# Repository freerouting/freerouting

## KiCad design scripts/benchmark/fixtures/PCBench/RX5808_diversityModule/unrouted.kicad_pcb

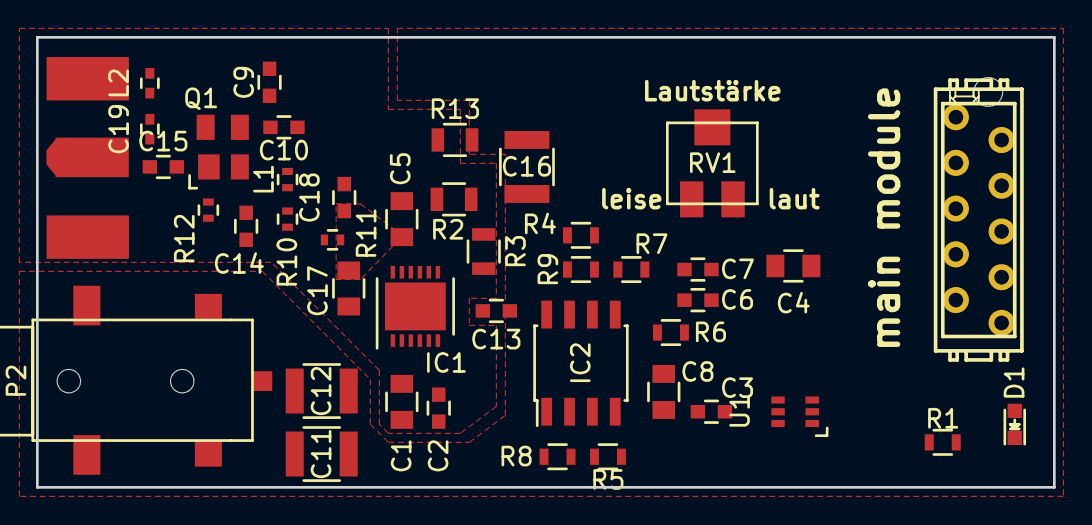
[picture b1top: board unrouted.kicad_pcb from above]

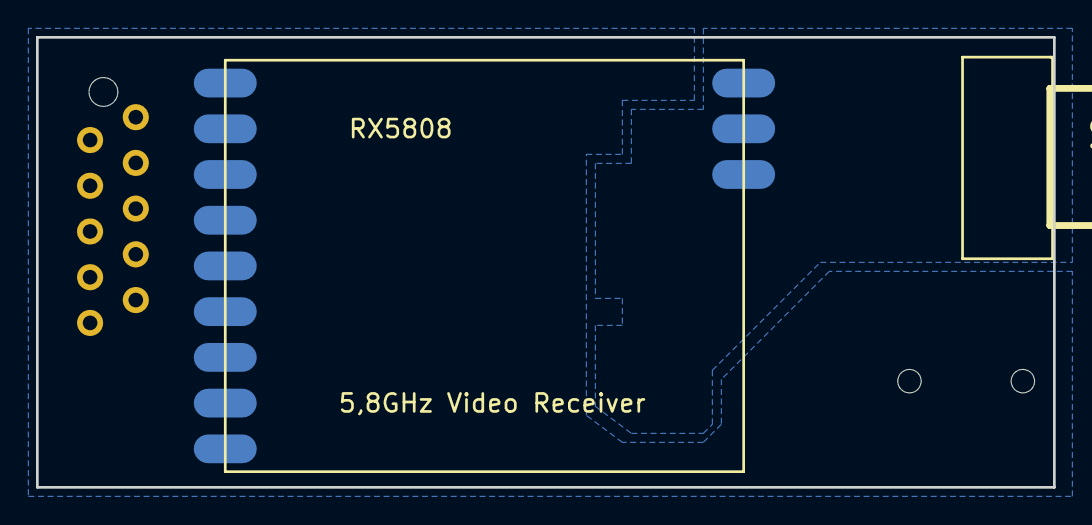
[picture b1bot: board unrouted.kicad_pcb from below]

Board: 2 copper layers, 56.5 x 25.0 mm, 44 parts (2 on the bottom side), 33 nets, no tracks yet.

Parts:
C1, C4, C5, C17: 10u; C_0805
C2: 10n; C_0603
C3, C13, C18: 100n; C_0603
C6, C7: 1u; C_0603
C8: 22u; C_0805
C9, C10: 1p; C_0603
C11, C12, C16: 100µ; C_1210
C14: 33pF; C_0603
C15: 22p; C_0603
C19: 2,2pF; C_0402
D1: red; LED_0603
IC1: LP38798; DFN-12-1EP_4x4mm_Pitch0.5mm
IC2: TDA1308A; SOIC-8_3.9x4.9mm_Pitch1.27mm
L1: 1,8nH; R_0402
L2: 1,8nH; C_0402
P1: CONN_02X05; MICROMATCH-10
P2: CONN_01X03; LUM1503-03
Q1: BFP840; SOT-143
R1: 220; R_0603
R2: 21k 0,1%; R_0805
R3: 14k 0,1%; R_0805
R4, R5: 10k; R_0603
R6, R7: 3,9k; R_0603
R8, R9: 39k; R_0603
R10, R11: 51; R_0402
R12: 27k; R_0402
R13: 0; R_0805
RV1: POT; Poti-SMD-Model-23A
SMA_E1: SMA_EDGE; SMA_EDGE_Johnson_142-0701-801
U1: sn74lvc1g3157; SC-70-6
U2: RX5808

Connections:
+5V: C1.1, C3.1, C4.1, C13.1, C16.1, IC1.1, IC1.2, IC1.3, IC1.5, IC2.8, P1.1, R4.1, U1.5, U2.8
/+3,0V: C5.1, C17.1, C18.1, IC1.10, IC1.11, IC1.12, R11.2
/audio1: P1.6, U1.3
/clk: P1.7, U2.6
/data: P1.3, U2.4
/rssi: P1.8, U2.9
/ss: P1.5, U2.5
/switch: D1.2, P1.9, U1.6
/video2: P1.4, U2.11
GND: C3.2, C4.2, C8.2, C13.2, C16.2, IC2.4, P1.2, P2.1, R1.2, R5.2, R13.1, RV1.3, U1.2, U2.7, U2.12
GNDA: C1.2, C2.2, C5.2, C9.2, C14.1, C17.2, C18.2, IC1.6, IC1.7, IC1.13, L2.2, Q1.2, Q1.4, R3.2, R13.2, SMA_E1.0, SMA_E1.2, U2.1, U2.3
unnamed: C2.1, IC1.4
unnamed: C6.1, R6.2
unnamed: C6.2, C7.2, RV1.2
unnamed: C7.1, R7.2
unnamed: C8.1, IC2.2, IC2.3, IC2.5, R4.2, R5.1, R6.1, R8.2
unnamed: C9.1, C10.1, L1.2, Q1.3
unnamed: C10.2, U2.2
unnamed: C11.1, IC2.1, R8.1
unnamed: C11.2, P2.2
unnamed: C12.1, IC2.7, R9.1
unnamed: C12.2, P2.3
unnamed: C14.2, R10.1, R11.1, R12.2
unnamed: C15.1, C19.1, SMA_E1.1
unnamed: C15.2, Q1.1, R12.1
unnamed: C19.2, L2.1
unnamed: D1.1, R1.1
unnamed: IC1.8, R2.2, R3.1
unnamed: IC1.9, R2.1
unnamed: IC2.6, R7.1, R9.2
unnamed: L1.1, R10.2
unnamed: RV1.1, U1.4
unnamed: U1.1, U2.10

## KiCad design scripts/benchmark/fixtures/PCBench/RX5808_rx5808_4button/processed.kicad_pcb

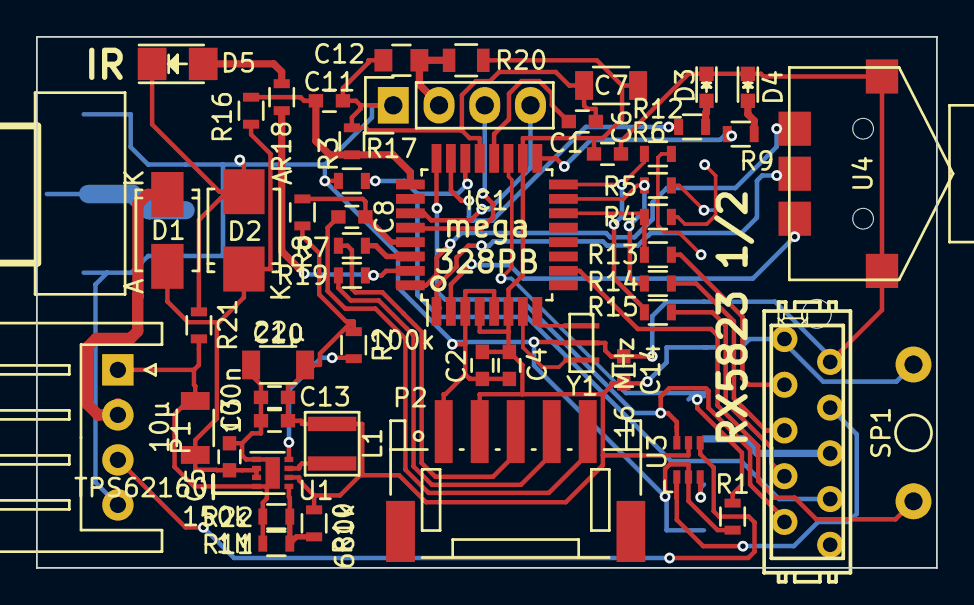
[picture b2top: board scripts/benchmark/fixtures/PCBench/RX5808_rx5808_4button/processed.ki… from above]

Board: 2 copper layers, 50.0 x 29.5 mm, 54 parts (1 on the bottom side), 47 nets.

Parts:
C1, C2, C3, C4, C6, C8, C9, C11, C13, C14: 100n; C_0603
C5: 10µ; C_1206
C7, C10: 22µ; C_1206
C12: 4,7u; C_0805
D1: B 140 F; SMA_Standard
D2: P6SMB 18A SMD; SMB_Standard
D3, D4: grün; LED_0603
D5: IR_EMITTER; LED_1206
IC1: ATMEGA328-A; TQFP-32_7x7mm_Pitch0.8mm
L1: 2,2µH 1,5A; NR3015
P1: CONN_01X04; JST_XH_S04B-XH-A_04x2.50mm_Angled
P2: CONN_01X05; JST_PH_S5B-PH-SM4-TB_05x2.00mm_Angled
P6: CONN_01X04; Pin_Header_Straight_1x04
P7: CONN_02X05; MICROMATCH-10
R1, R2, R3: 100k; R_0603
R4, R5, R6, R7, R13, R14, R15, R17, R19: 1k; R_0603
R8: 10k; R_0603
R9, R12: 220; R_0603
R10: 680k; R_0603
R11: 1M; R_0603
R16: 15k; R_0603
R18: 100; R_0603
R20: 10; R_0805
R21: brücke; R_0603
R22: 150k; R_0603
SMA_E1: SMA_EDGE; SMA_EDGE_Johnson_142-0701-801
SP1: BUZ; Buzzer_12x9.5RM7.6
U1: TPS62160; DFN-8-1EP_2x2mm_Pitch0.5mm
U2: RX5808
U3: sn74lvc1g3157; SC-70-6
U4: MCPL3-BC-V; MCPL3-AC-V
Y1: 16 MHz; CerOsc_3,2x1,3

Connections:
+5V: C2.1, C4.1, C6.1, C7.1, C9.1, C10.1, C13.1, C14.1, IC1.4, IC1.6, IC1.18, L1.2, P2.2, P7.1, R2.2, R8.1, R10.1, R20.2, SP1.1, U1.6, U2.8, U3.5
+12V: C3.1, C5.1, D1.2, D2.1, R16.2, U1.2, U1.3
/Audio1: P7.6, U2.10
/DTR: C8.2, P2.5
/Funk1_clk: R6.1, U2.6
/Funk1_data: R4.1, U2.4
/Funk1_ss: R5.1, U2.5
/Funk2_clk: P7.7, R15.1
/Funk2_data: P7.3, R13.1
/Funk2_ss: P7.5, R14.1
/VidOut: P1.3, U3.4
/Video1: U2.11, U3.3
/Video2: P7.4, U3.1
/adc_12V: C11.1, IC1.25, R16.1, R17.2
/buzzer: IC1.10, SP1.2
/down: IC1.2, U4.2
/led1: IC1.23, R12.2
/led2: IC1.24, P7.9, U3.6
/led3: IC1.17, R9.2
/miso: IC1.16, R6.2, R15.2
/mode: IC1.1, U4.3
/mosi: IC1.15, R5.2, R14.2
/reset: C8.1, IC1.29, R8.2
/rssi1: IC1.19, R1.1, U2.9
/rssi2: IC1.22, P7.8, R3.1
/rxd: P2.3, R7.1
/scl: IC1.28, P6.3
/sda: IC1.27, P6.4
/ss: IC1.14, R4.2, R13.2
/txd: P2.4, R19.2
/up: IC1.32, U4.1
GND: C1.2, C2.2, C4.2, C6.2, C7.2, C11.2, C12.2, C14.2, D2.2, D3.1, D4.1, D5.1, IC1.3, IC1.5, IC1.21, P1.4, P2.1, P6.1, P7.2, R1.2, R3.2, R17.1, R21.2, SMA_E1.0, SMA_E1.2, U2.1, U2.3, U2.7, U2.12, U3.2, U4.4, U4.5, Y1.2
GNDPWR: C3.2, C5.2, C9.2, C10.2, C13.2, P1.1, R11.2, R21.1, R22.2, U1.1, U1.4, U1.EP
unnamed: C1.1, IC1.20
unnamed: C12.1, P6.2, R20.1
unnamed: D1.1, P1.2
unnamed: D3.2, R12.1
unnamed: D4.2, R9.1
unnamed: D5.2, R18.2
unnamed: IC1.7, Y1.3
unnamed: IC1.8, Y1.1
unnamed: IC1.30, R7.2
unnamed: IC1.31, R18.1, R19.1
unnamed: L1.1, U1.7
unnamed: R2.1, U1.8
unnamed: R10.2, R11.1, R22.1, U1.5
unnamed: SMA_E1.1, U2.2

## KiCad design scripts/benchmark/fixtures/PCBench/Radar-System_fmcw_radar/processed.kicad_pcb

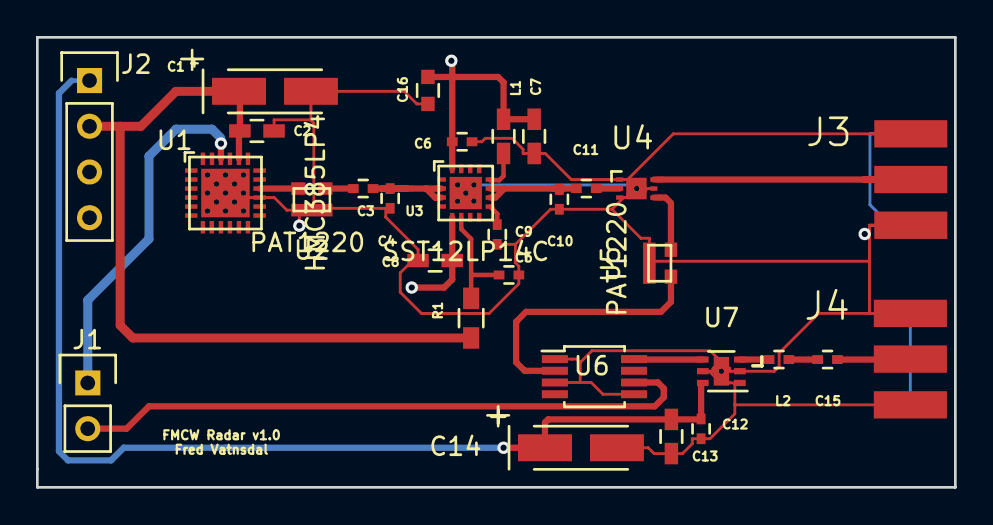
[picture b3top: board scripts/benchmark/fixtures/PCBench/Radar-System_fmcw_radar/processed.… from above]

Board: 4 copper layers, 51.0 x 25.0 mm, 30 parts (0 on the bottom side), 21 nets.

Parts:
C1: 4.7uF; TantalC_SizeA_EIA-3216_HandSoldering
C2, C13: 10nF; C_0603_HandSoldering
C3, C11: 47pF; C_0402
C4: 1.2pF; C_0402
C5, C6: 100pF; C_0402
C7, C8: 0.1uF; C_0603_HandSoldering
C9: 10pF; C_0402
C10: 2.0pF; C_0402
C12: 1nF; C_0402
C14: 2.2uF; TantalC_SizeA_EIA-3216_HandSoldering
C15: 2.7pF; C_0402
C16: 10uF; C_0603
J1: conn_2; Pin_Header_Straight_1x02
J2: conn_4; Pin_Header_Straight_1x04
J3, J4: conn_sma; CONSMA003.062
L1: 12nH; C_0603_HandSoldering
L2: 2.0nH; C_0402
R1: 30; R_0603_HandSoldering
U1: HMC385LP4; VQFN-24
U2, U5: PAT1220
U3: SST12LP14C; VQFN-16
U4: SKY16406-381LF; SOIC-6
U6: HMC272AMS8; MSOP-8_3x3mm_Pitch0.65mm
U7: HMC667LP2; DFN-6_2x2

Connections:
/3.3V: C6.1, C7.1, C8.1, C16.1, J2.3, L1.1, U3.5, U3.16
/3V: C1.1, C2.1, J2.2, R1.1, U1.20
/3V/5V: C12.1, C13.1, C14.1, J2.1, U7.6
/IF_OUT: J1.2, U6.6
/VTUNE: J1.1, U1.22
GND: C1.2, C2.2, C4.2, C5.2, C6.2, C7.2, C8.2, C9.2, C10.2, C12.2, C13.2, C14.2, C16.2, J2.4, J3.2, J4.2, U1.15, U1.PAD, U2.3, U3.PAD, U4.1, U4.3, U4.5, U4.PAD, U5.3, U6.1, U6.3, U6.5, U7.1, U7.2, U7.5, U7.PAD
unnamed: C3.1, C4.1, U3.2, U3.3
unnamed: C3.2, U2.2
unnamed: C5.1, R1.2, U3.6
unnamed: C9.1, U3.9
unnamed: C10.1, C11.2, U3.10, U3.11
unnamed: C11.1, U4.2
unnamed: C15.1, J4.1
unnamed: C15.2, L2.2
unnamed: J3.1, U4.6
unnamed: L1.2, U3.12
unnamed: L2.1, U7.3
unnamed: U1.16, U2.1
unnamed: U4.4, U5.1
unnamed: U5.2, U6.2
unnamed: U6.8, U7.4

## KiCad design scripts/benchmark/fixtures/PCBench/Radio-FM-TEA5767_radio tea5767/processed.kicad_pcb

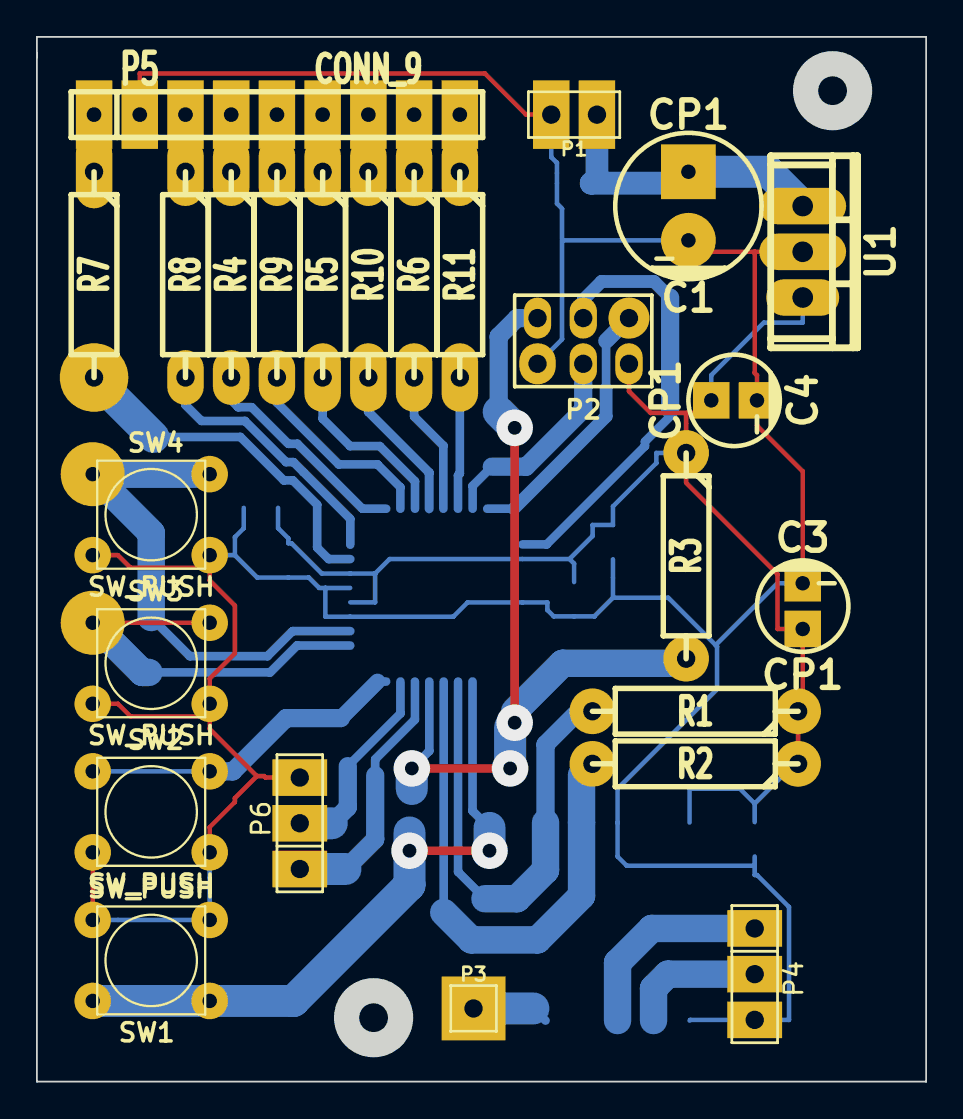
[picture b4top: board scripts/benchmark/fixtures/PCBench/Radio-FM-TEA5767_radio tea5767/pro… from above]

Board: 2 copper layers, 49.4 x 58.0 mm, 33 parts (0 on the bottom side), 34 nets.

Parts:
C1: CP1; CP_8x13mm
C2, C5, C6, C7, C8, C9: C; c_0805
C3, C4: CP1; CP_5x11mm
IC1: ATMEGA8-AI; TQFP32
P1: CONN_2; PIN_ARRAY_2X1
P2: CONN_3X2; pin_array_3x2
P3: CONN_1; PIN_ARRAY_1
P4, P6: CONN_3; PIN_ARRAY_3X1
P5: CONN_9; SIL-9
R1, R2, R3, R4, R5, R6, R7, R8, R9, R10, R11: R; R4-5
SW1, SW2, SW3, SW4: SW_PUSH; 6x6mm_pad_4,5x6,5mm
U1: 7805_TO-220; TO-220
U3: TEA5767; TEA5767_SMD

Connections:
+5V: C3.1, C4.1, C5.1, C6.1, C7.1, C8.1, C9.1, IC1.4, IC1.6, IC1.18, P2.2, R1.1, R2.1, R3.1, U1.3, U3.5
GND: C1.2, C2.2, C3.2, C4.2, C5.2, C6.2, C7.2, C8.2, C9.2, IC1.3, IC1.5, IC1.21, P1.2, P2.6, P4.3, P5.2, P6.3, SW1.2, SW2.2, SW3.2, SW4.2, U1.2, U3.3, U3.6
MISO: IC1.16, P2.1
MOSI: IC1.15, P2.4
unnamed: P5.1, R7.1
unnamed: P5.3, R8.1
unnamed: P3.1, U3.10
unnamed: P5.9, R11.1
unnamed: P5.8, R6.1
unnamed: P5.7, R10.1
unnamed: P5.6, R5.1
unnamed: P5.5, R9.1
unnamed: P5.4, R4.1
unnamed: C1.1, C2.1, P1.1, U1.1
unnamed: P4.2, U3.7
unnamed: P4.1, U3.8
RST: IC1.29, P2.5, R3.2
RXD: IC1.30, P6.1
SCK: IC1.17, P2.3
SCL: IC1.28, R2.2, U3.2
SDA: IC1.27, R1.2, U3.1
TXD: IC1.31, P6.2
btn_1: IC1.26, SW1.1
btn_2: IC1.32, SW2.1
btn_3: IC1.1, SW3.1
btn_4: IC1.2, SW4.1
seg_A: IC1.7, R7.2
seg_B: IC1.8, R8.2
seg_C: IC1.11, R5.2
seg_D: IC1.12, R10.2
seg_DP: IC1.14, R11.2
seg_E: IC1.13, R6.2
seg_F: IC1.9, R4.2
seg_G: IC1.10, R9.2
